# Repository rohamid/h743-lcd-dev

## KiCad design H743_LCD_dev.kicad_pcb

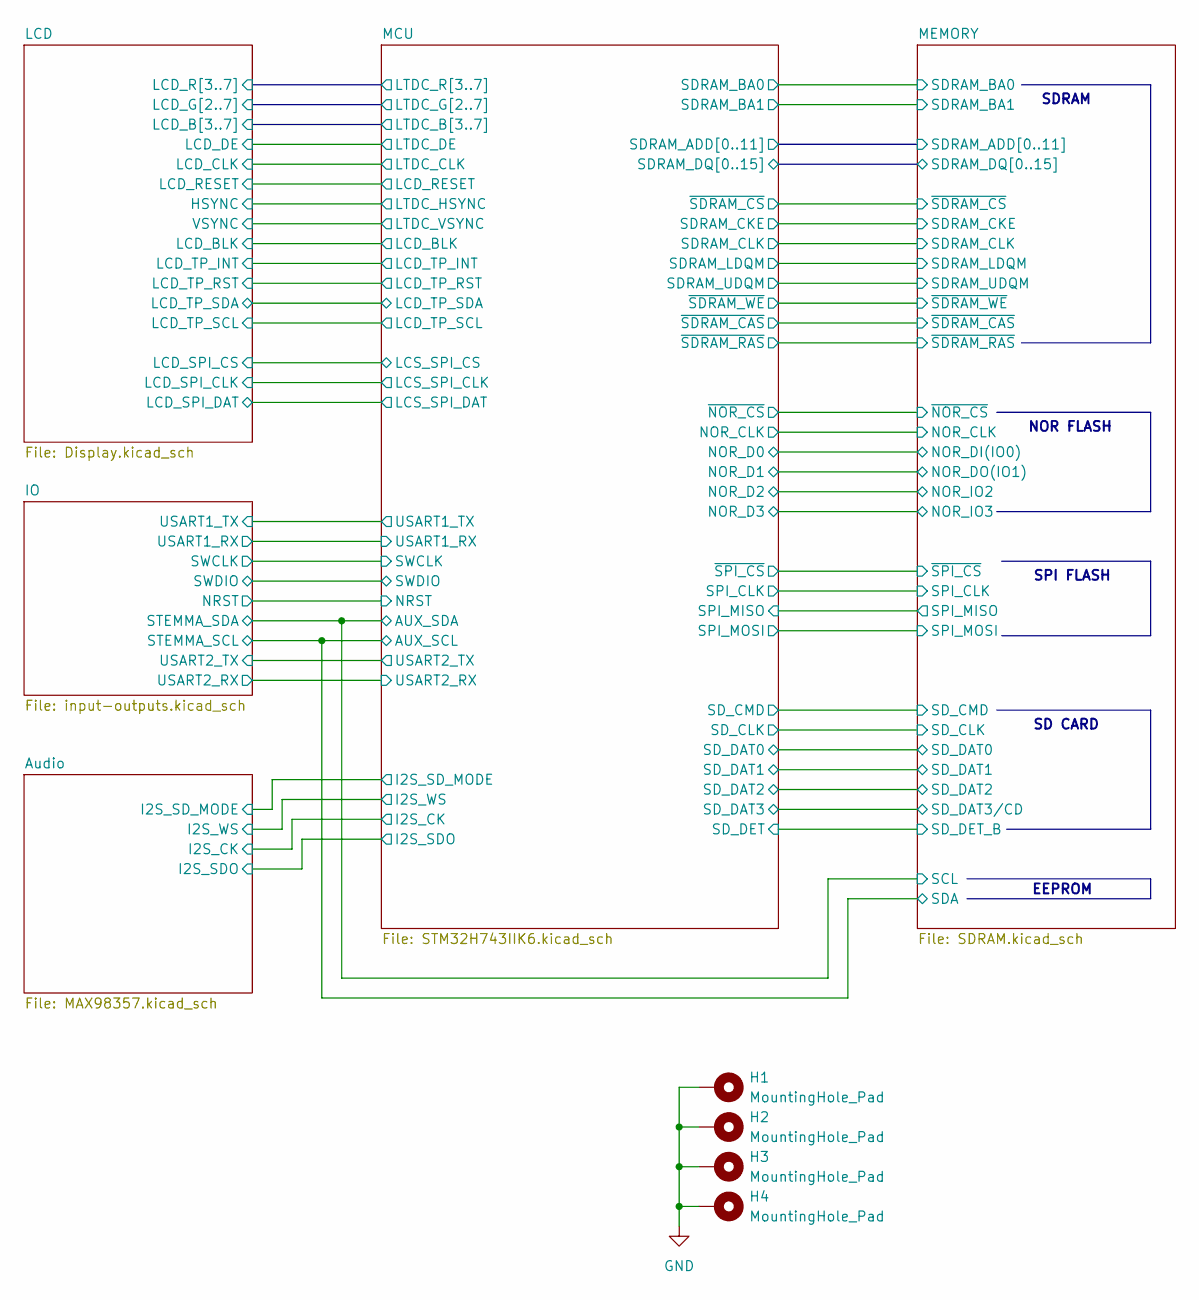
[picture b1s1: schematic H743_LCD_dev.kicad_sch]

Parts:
H1, H2, H3, H4: MountingHole_Pad; MountingHole_3.2mm_M3_Pad_Via

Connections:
GND: H1.1, H2.1, H3.1, H4.1; also elsewhere on the board

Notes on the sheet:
SD CARD
NOR FLASH
SPI FLASH
SDRAM
EEPROM

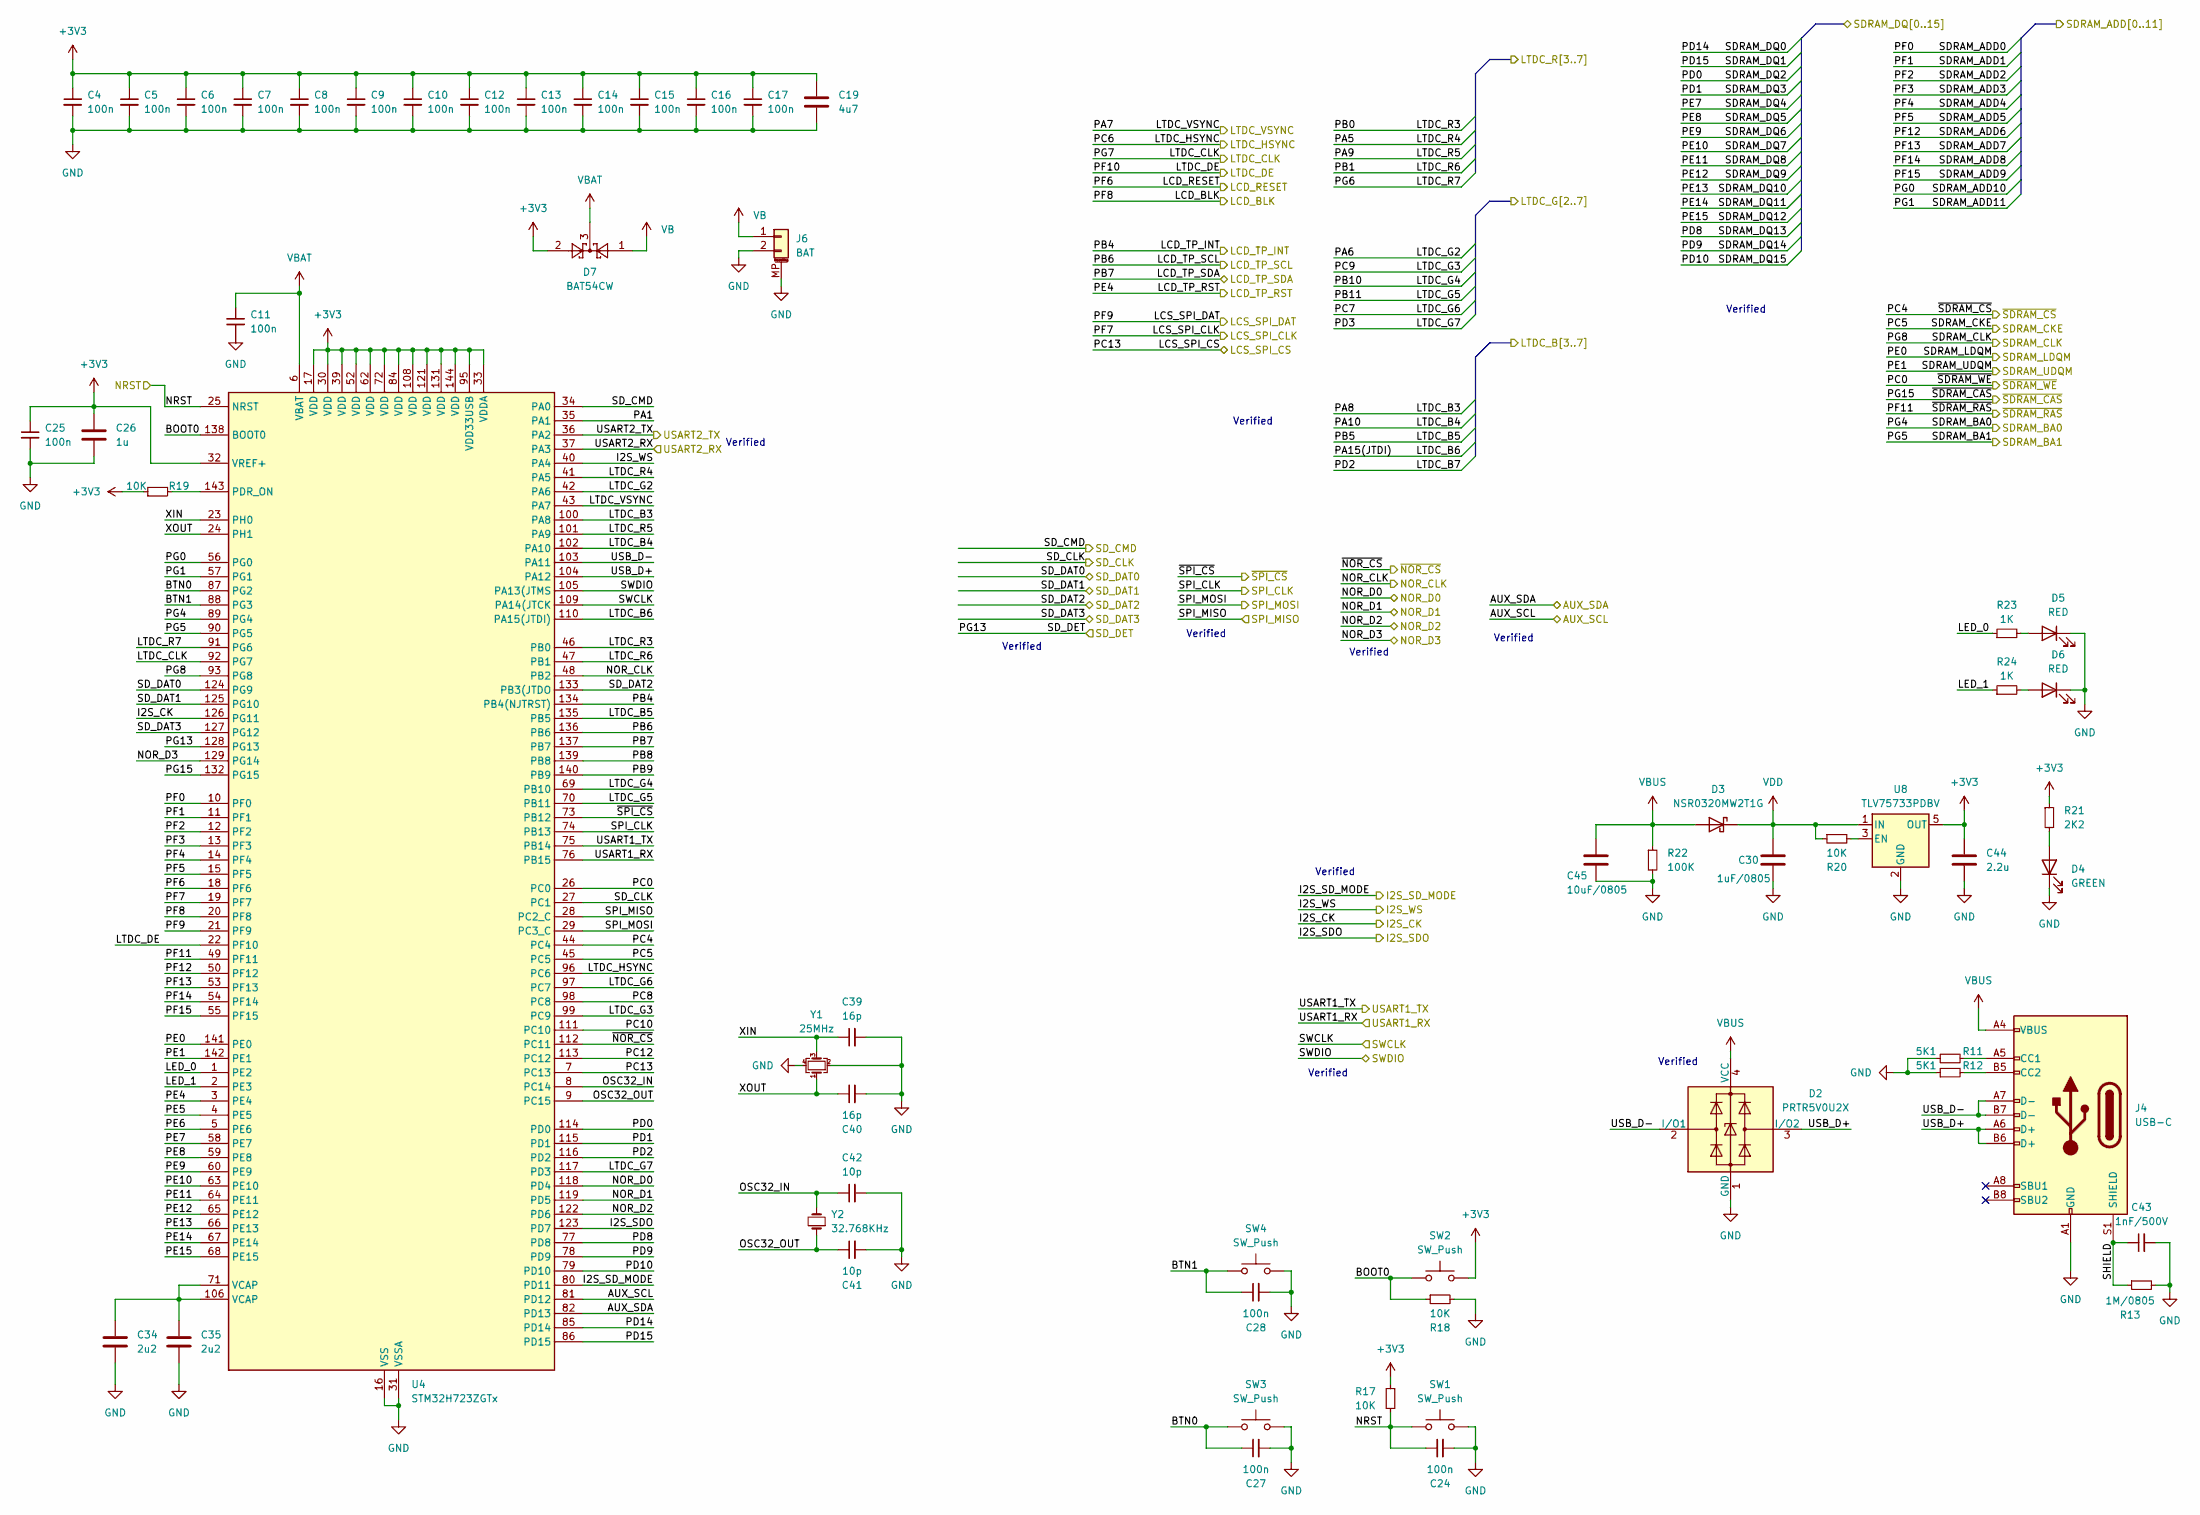
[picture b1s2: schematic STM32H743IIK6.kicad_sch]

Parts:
C4, C5, C6, C7, C8, C9, C10, C11, C12, C13, C14, C15, C16, C17, C24, C25, C27, C28: 100n; C_0402_1005Metric; JLCPCB Part # C307331
C19: 4u7; C_0603_1608Metric; JLCPCB Part # C19666
C26: 1u; C_0603_1608Metric; JLCPCB Part # C15849
C30: 1uF/0805; C_0805_2012Metric; JLCPCB Part # C28323
C34, C35: 2u2; C_0603_1608Metric; JLCPCB Part # C23630
C39, C40: 16p; C_0402_1005Metric; JLCPCB Part # C77590
C41, C42: 10p; C_0402_1005Metric; JLCPCB Part # C32949
C43: 1nF/500V; C_1206_3216Metric; JLCPCB Part # C35216
C44: 2.2u; C_0805_2012Metric; JLCPCB Part # C377773
C45: 10uF/0805; C_0805_2012Metric; JLCPCB Part # C440198
D2: PRTR5V0U2X; SOT-143; JLCPCB Part # C12333
D3: NSR0320MW2T1G; D_SOD-323; JLCPCB Part # C48192
D4: GREEN; LED_0805_2012Metric; JLCPCB Part # C2297
D5, D6: RED; LED_0805_2012Metric; JLCPCB Part # C84256
D7: BAT54CW; SOT-23; JLCPCB Part # C37704
J4: USB-C; USB_C_Receptacle_G-Switch_GT-USB-7010ASV; JLCPCB Part # C963412
J6: BAT; Hirose_DF13C_CL535-0402-2-51_1x02-1MP_P1.25mm_Vertical; JLCPCB Part # C7419891
R11, R12: 5K1; R_0402_1005Metric; JLCPCB Part # C25905
R13: 1M/0805; R_0805_2012Metric; JLCPCB Part # C17514
R17, R18, R19, R20: 10K; R_0402_1005Metric; JLCPCB Part # C25744
R21: 2K2; R_0402_1005Metric; JLCPCB Part # C25879
R22: 100K; R_0402_1005Metric; JLCPCB Part # C25741
R23, R24: 1K; R_0402_1005Metric; JLCPCB Part # C11702
SW1, SW2, SW3, SW4: SW_Push; SW_SPST_PTS810; JLCPCB Part # C127488
U4: STM32H723ZGTx; LQFP-144_20x20mm_P0.5mm; JLCPCB Part # C730146
U8: TLV75733PDBV; SOT-23-5; JLCPCB Part # C485517
Y1: 25MHz; Crystal_SMD_2520-4Pin_2.5x2.0mm; JLCPCB Part # C255954
Y2: 32.768KHz; Crystal_SMD_2012-2Pin_2.0x1.2mm; JLCPCB Part # C99009

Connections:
+3V3: C4.1, C5.1, C6.1, C7.1, C8.1, C9.1, C10.1, C12.1, C13.1, C14.1, C15.1, C16.1, C17.1, C19.1, C25.1, C26.1, C44.1, D7.2, R17.1, R19.1, R21.1, SW2.2, U4.17 (VDD), U4.30 (VDD), U4.32 (VREF+), U4.33 (VDDA), U4.39 (VDD), U4.52 (VDD), U4.62 (VDD), U4.72 (VDD), U4.84 (VDD), U4.95 (VDD33USB), U4.108 (VDD), U4.121 (VDD), U4.131 (VDD), U4.144 (VDD), U8.5 (OUT); also elsewhere on the board
/IO/NRST: C24.1, R17.2, SW1.1, U4.25 (NRST); also elsewhere on the board
/IO/STEMMA_SCL: U4.81 (PD12); also elsewhere on the board
/IO/STEMMA_SDA: U4.82 (PD13); also elsewhere on the board
/IO/SWCLK: U4.109 (PA14(JTCK); also elsewhere on the board
/IO/SWDIO: U4.105 (PA13(JTMS); also elsewhere on the board
/IO/USART1_RX: U4.76 (PB15); also elsewhere on the board
/IO/USART1_TX: U4.75 (PB14); also elsewhere on the board
/IO/USART2_RX: U4.37 (PA3); also elsewhere on the board
/IO/USART2_TX: U4.36 (PA2); also elsewhere on the board
/LCD/HSYNC: U4.96 (PC6); also elsewhere on the board
/LCD/LCD_B3: U4.100 (PA8); also elsewhere on the board
/LCD/LCD_B4: U4.102 (PA10); also elsewhere on the board
/LCD/LCD_B5: U4.135 (PB5); also elsewhere on the board
/LCD/LCD_B6: U4.110 (PA15(JTDI)); also elsewhere on the board
/LCD/LCD_B7: U4.116 (PD2); also elsewhere on the board
/LCD/LCD_BLK: U4.20 (PF8); also elsewhere on the board
/LCD/LCD_CLK: U4.92 (PG7); also elsewhere on the board
/LCD/LCD_DE: U4.22 (PF10); also elsewhere on the board
/LCD/LCD_G2: U4.42 (PA6); also elsewhere on the board
/LCD/LCD_G3: U4.99 (PC9); also elsewhere on the board
/LCD/LCD_G4: U4.69 (PB10); also elsewhere on the board
/LCD/LCD_G5: U4.70 (PB11); also elsewhere on the board
/LCD/LCD_G6: U4.97 (PC7); also elsewhere on the board
/LCD/LCD_G7: U4.117 (PD3); also elsewhere on the board
/LCD/LCD_R3: U4.46 (PB0); also elsewhere on the board
/LCD/LCD_R4: U4.41 (PA5); also elsewhere on the board
/LCD/LCD_R5: U4.101 (PA9); also elsewhere on the board
/LCD/LCD_R6: U4.47 (PB1); also elsewhere on the board
/LCD/LCD_R7: U4.91 (PG6); also elsewhere on the board
/LCD/LCD_RESET: U4.18 (PF6); also elsewhere on the board
/LCD/LCD_SPI_CLK: U4.19 (PF7); also elsewhere on the board
/LCD/LCD_SPI_CS: U4.7 (PC13); also elsewhere on the board
/LCD/LCD_SPI_DAT: U4.21 (PF9); also elsewhere on the board
/LCD/LCD_TP_INT: U4.134 (PB4(NJTRST)); also elsewhere on the board
/LCD/LCD_TP_RST: U4.3 (PE4); also elsewhere on the board
/LCD/LCD_TP_SCL: U4.136 (PB6); also elsewhere on the board
/LCD/LCD_TP_SDA: U4.137 (PB7); also elsewhere on the board
/LCD/VSYNC: U4.43 (PA7); also elsewhere on the board
/MCU/BOOT0: R18.1, SW2.1, U4.138 (BOOT0)
/MCU/BTN0: C27.1, SW3.1, U4.87 (PG2)
/MCU/BTN1: C28.1, SW4.1, U4.88 (PG3)
/MCU/I2S_CK: U4.126 (PG11); also elsewhere on the board
/MCU/I2S_SDO: U4.123 (PD7); also elsewhere on the board
/MCU/I2S_SD_MODE: U4.80 (PD11); also elsewhere on the board
/MCU/I2S_WS: U4.40 (PA4); also elsewhere on the board
/MCU/LED_0: R23.1, U4.1 (PE2)
/MCU/LED_1: R24.1, U4.2 (PE3)
/MCU/NOR_CLK: U4.48 (PB2); also elsewhere on the board
/MCU/NOR_D0: U4.118 (PD4); also elsewhere on the board
/MCU/NOR_D1: U4.119 (PD5); also elsewhere on the board
/MCU/NOR_D2: U4.122 (PD6); also elsewhere on the board
/MCU/NOR_D3: U4.129 (PG14); also elsewhere on the board
/MCU/OSC32_IN: C42.1, U4.8 (PC14), Y2.2
/MCU/OSC32_OUT: C41.1, U4.9 (PC15), Y2.1
/MCU/PA1: U4.35 (PA1)
/MCU/PB8: U4.139 (PB8)
/MCU/PB9: U4.140 (PB9)
/MCU/PC0: U4.26 (PC0); also elsewhere on the board
/MCU/PC4: U4.44 (PC4); also elsewhere on the board
/MCU/PC5: U4.45 (PC5); also elsewhere on the board
/MCU/PC8: U4.98 (PC8)
/MCU/PC10: U4.111 (PC10)
/MCU/PC12: U4.113 (PC12)
/MCU/PE0: U4.141 (PE0); also elsewhere on the board
/MCU/PE1: U4.142 (PE1); also elsewhere on the board
/MCU/PE5: U4.4 (PE5)
/MCU/PE6: U4.5 (PE6)
/MCU/PF11: U4.49 (PF11); also elsewhere on the board
/MCU/PG4: U4.89 (PG4); also elsewhere on the board
/MCU/PG5: U4.90 (PG5); also elsewhere on the board
/MCU/PG8: U4.93 (PG8); also elsewhere on the board
/MCU/PG13: U4.128 (PG13); also elsewhere on the board
/MCU/PG15: U4.132 (PG15); also elsewhere on the board
/MCU/SDRAM_ADD0: U4.10 (PF0); also elsewhere on the board
/MCU/SDRAM_ADD1: U4.11 (PF1); also elsewhere on the board
/MCU/SDRAM_ADD2: U4.12 (PF2); also elsewhere on the board
/MCU/SDRAM_ADD3: U4.13 (PF3); also elsewhere on the board
/MCU/SDRAM_ADD4: U4.14 (PF4); also elsewhere on the board
/MCU/SDRAM_ADD5: U4.15 (PF5); also elsewhere on the board
/MCU/SDRAM_ADD6: U4.50 (PF12); also elsewhere on the board
/MCU/SDRAM_ADD7: U4.53 (PF13); also elsewhere on the board
/MCU/SDRAM_ADD8: U4.54 (PF14); also elsewhere on the board
/MCU/SDRAM_ADD9: U4.55 (PF15); also elsewhere on the board
/MCU/SDRAM_ADD10: U4.56 (PG0); also elsewhere on the board
/MCU/SDRAM_ADD11: U4.57 (PG1); also elsewhere on the board
/MCU/SDRAM_DQ0: U4.85 (PD14); also elsewhere on the board
/MCU/SDRAM_DQ1: U4.86 (PD15); also elsewhere on the board
/MCU/SDRAM_DQ2: U4.114 (PD0); also elsewhere on the board
/MCU/SDRAM_DQ3: U4.115 (PD1); also elsewhere on the board
/MCU/SDRAM_DQ4: U4.58 (PE7); also elsewhere on the board
/MCU/SDRAM_DQ5: U4.59 (PE8); also elsewhere on the board
/MCU/SDRAM_DQ6: U4.60 (PE9); also elsewhere on the board
/MCU/SDRAM_DQ7: U4.63 (PE10); also elsewhere on the board
/MCU/SDRAM_DQ8: U4.64 (PE11); also elsewhere on the board
/MCU/SDRAM_DQ9: U4.65 (PE12); also elsewhere on the board
/MCU/SDRAM_DQ10: U4.66 (PE13); also elsewhere on the board
/MCU/SDRAM_DQ11: U4.67 (PE14); also elsewhere on the board
/MCU/SDRAM_DQ12: U4.68 (PE15); also elsewhere on the board
/MCU/SDRAM_DQ13: U4.77 (PD8); also elsewhere on the board
/MCU/SDRAM_DQ14: U4.78 (PD9); also elsewhere on the board
/MCU/SDRAM_DQ15: U4.79 (PD10); also elsewhere on the board
/MCU/SD_CLK: U4.27 (PC1); also elsewhere on the board
/MCU/SD_CMD: U4.34 (PA0); also elsewhere on the board
/MCU/SD_DAT0: U4.124 (PG9); also elsewhere on the board
/MCU/SD_DAT1: U4.125 (PG10); also elsewhere on the board
/MCU/SD_DAT2: U4.133 (PB3(JTDO); also elsewhere on the board
/MCU/SD_DAT3: U4.127 (PG12); also elsewhere on the board
/MCU/SHIELD: C43.1, J4.S1 (SHIELD), R13.1
/MCU/SPI_CLK: U4.74 (PB13); also elsewhere on the board
/MCU/SPI_MISO: U4.28 (PC2_C); also elsewhere on the board
/MCU/SPI_MOSI: U4.29 (PC3_C); also elsewhere on the board
/MCU/USB_D+: D2.3 (I/O2), J4.A6 (D+), J4.B6 (D+), U4.104 (PA12)
/MCU/USB_D-: D2.2 (I/O1), J4.A7 (D-), J4.B7 (D-), U4.103 (PA11)
/MCU/XIN: C39.1, U4.23 (PH0), Y1.3
/MCU/XOUT: C40.1, U4.24 (PH1), Y1.1
/MCU/~NOR_CS: U4.112 (PC11); also elsewhere on the board
/MCU/~SPI_CS: U4.73 (PB12); also elsewhere on the board
GND: C4.2, C5.2, C6.2, C7.2, C8.2, C9.2, C10.2, C11.2, C12.2, C13.2, C14.2, C15.2, C16.2, C17.2, C19.2, C24.2, C25.2, C26.2, C27.2, C28.2, C30.2, C34.2, C35.2, C39.2, C40.2, C41.2, C42.2, C43.2, C44.2, C45.2, D2.1 (GND), D4.1 (K), D5.1 (K), D6.1 (K), J4.A1 (GND), J4.A12 (GND), J4.B1 (GND), J4.B12 (GND), J6.2, J6.MP (MountPin), R11.1, R12.1, R13.2, R18.2, R22.2, SW1.2, SW3.2, SW4.2, U4.16 (VSS), U4.31 (VSSA), U4.38 (VSS), U4.51 (VSS), U4.61 (VSS), U4.83 (VSS), U4.94 (VSS), U4.107 (VSS), U4.120 (VSS), U4.130 (VSS), U8.2 (GND), Y1.2, Y1.4; also elsewhere on the board
unnamed: C34.1, C35.1, U4.71 (VCAP), U4.106 (VCAP)
unnamed: D4.2 (A), R21.2
unnamed: D5.2 (A), R23.2
unnamed: D6.2 (A), R24.2
unnamed: J4.A5 (CC1), R11.2
unnamed: J4.B5 (CC2), R12.2
unnamed: R19.2, U4.143 (PDR_ON)
unnamed: R20.2, U8.3 (EN)
VB: D7.1, J6.1
VBAT: C11.1, D7.3, U4.6 (VBAT)
VBUS: C45.1, D2.4 (VCC), D3.2 (A), J4.A4 (VBUS), J4.A9 (VBUS), J4.B4 (VBUS), J4.B9 (VBUS), R22.1
VDD: C30.1, D3.1 (K), R20.1, U8.1 (IN); also elsewhere on the board

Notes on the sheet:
Verified

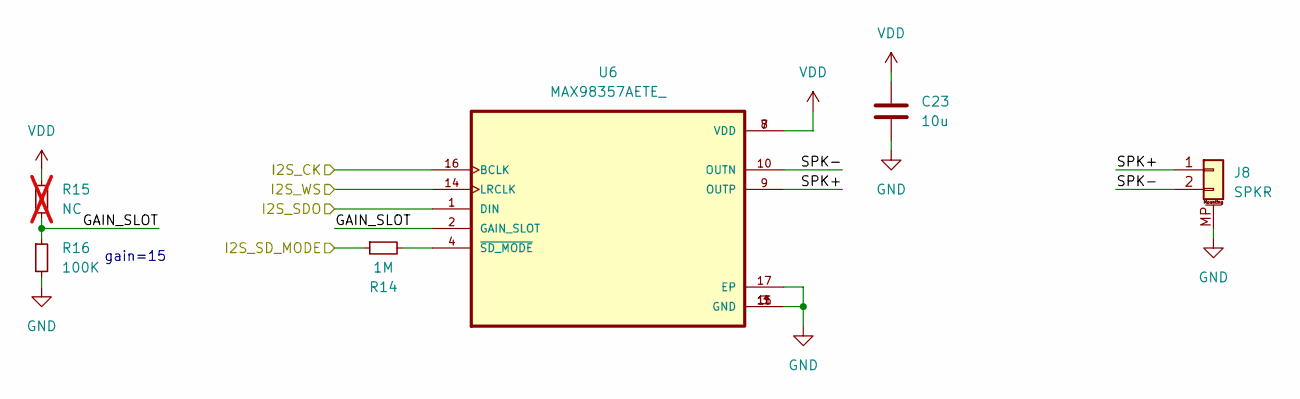
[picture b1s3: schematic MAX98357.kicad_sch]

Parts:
C23: 10u; C_0603_1608Metric; JLCPCB Part # C96446
J8: SPKR; Hirose_DF13C_CL535-0402-2-51_1x02-1MP_P1.25mm_Vertical; JLCPCB Part # C7419891
R14: 1M; R_0402_1005Metric; JLCPCB Part # C26083
R15: NC; R_0402_1005Metric; not fitted
R16: 100K; R_0402_1005Metric; JLCPCB Part # C25741
U6: MAX98357AETE_; QFN50P300X300X80-17N; JLCPCB Part # C910544

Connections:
/Audio/GAIN_SLOT: R15.2, R16.1, U6.2 (GAIN_SLOT)
/Audio/SPK+: J8.1, U6.9 (OUTP)
/Audio/SPK-: J8.2, U6.10 (OUTN)
/MCU/I2S_CK: U6.16 (BCLK); also elsewhere on the board
/MCU/I2S_SDO: U6.1 (DIN); also elsewhere on the board
/MCU/I2S_SD_MODE: R14.1; also elsewhere on the board
/MCU/I2S_WS: U6.14 (LRCLK); also elsewhere on the board
GND: C23.2, J8.MP (MountPin), R16.2, U6.3 (GND), U6.11 (GND), U6.15 (GND), U6.17 (EP); also elsewhere on the board
unnamed: R14.2, U6.4 (~SD_MODE)
VDD: C23.1, R15.1, U6.7 (VDD), U6.8 (VDD); also elsewhere on the board

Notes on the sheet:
gain=15

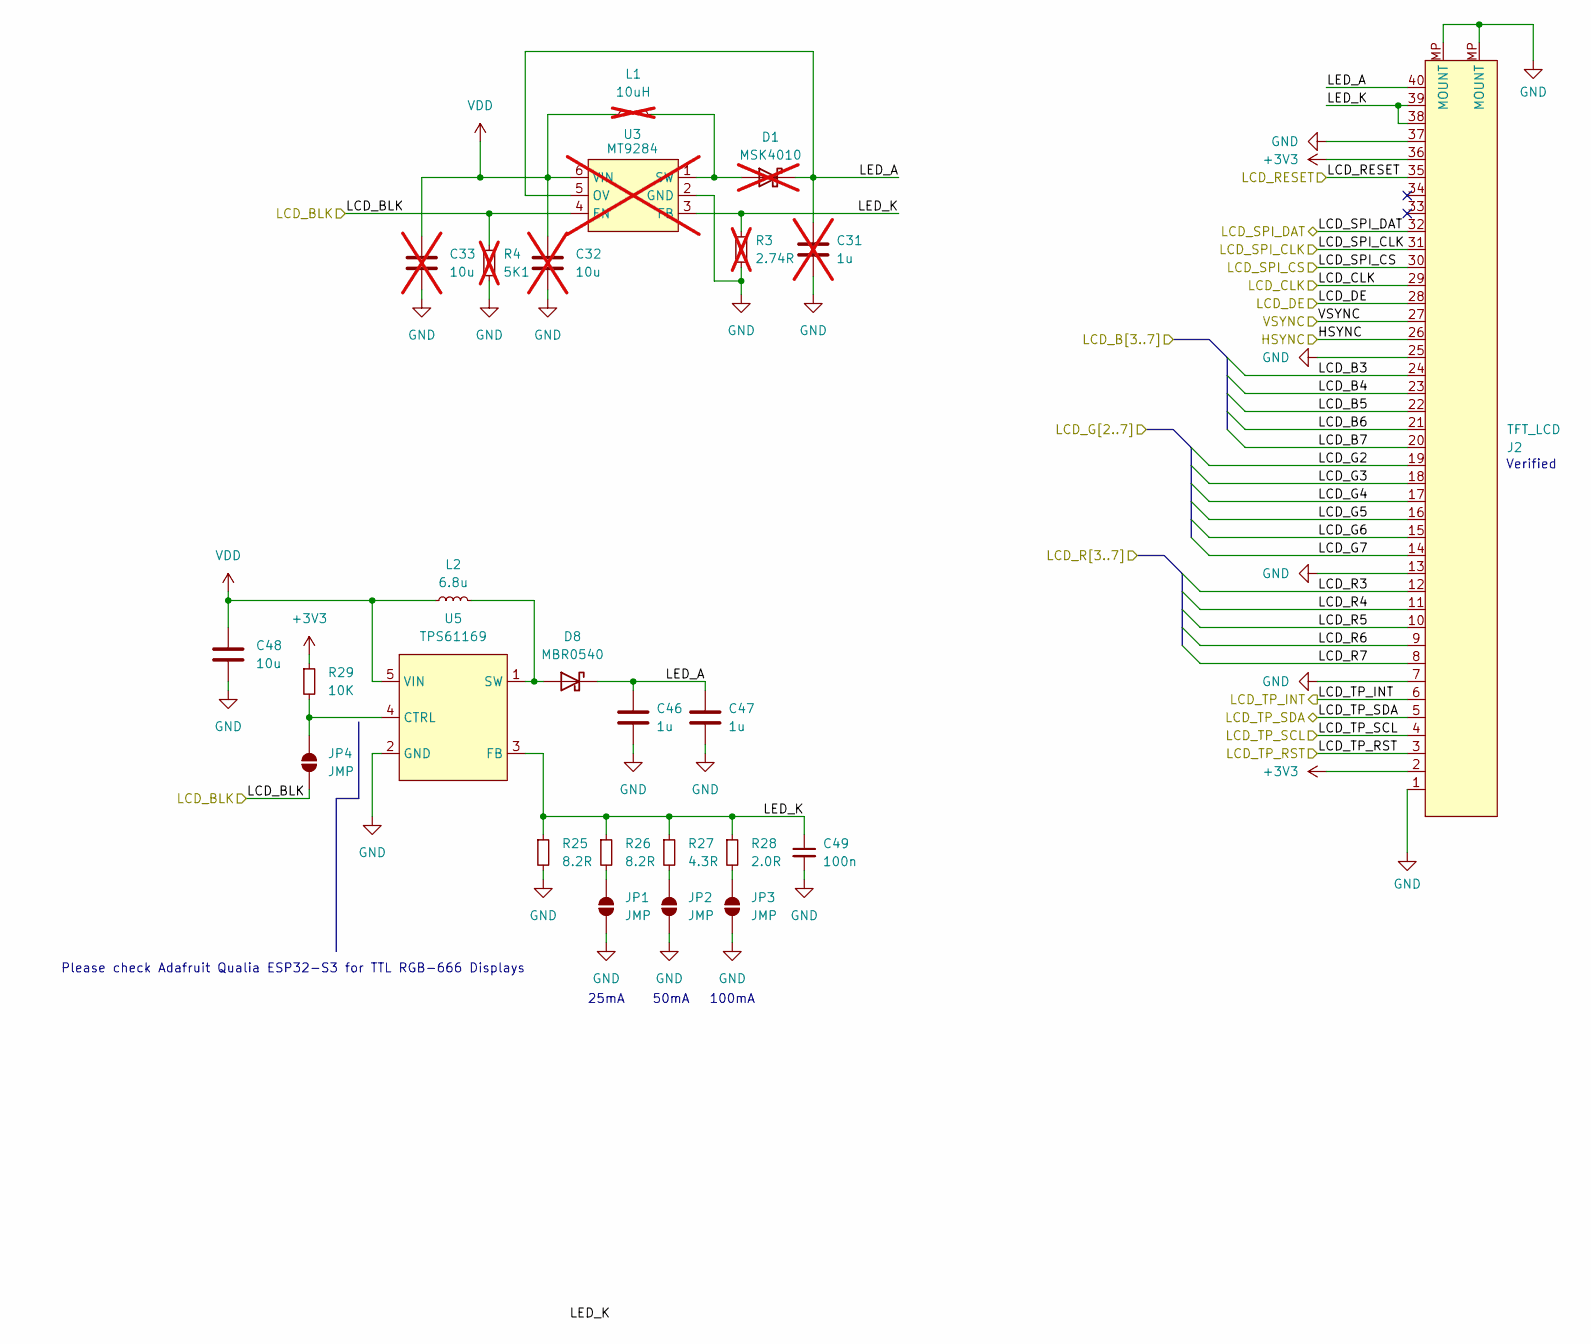
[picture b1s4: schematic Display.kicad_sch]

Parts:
C31: 1u; C_0603_1608Metric; JLCPCB Part # C15849; not fitted
C32, C33: 10u; C_0603_1608Metric; JLCPCB Part # C96446; not fitted
C46, C47: 1u; C_0603_1608Metric; JLCPCB Part # C15849
C48: 10u; C_0603_1608Metric; JLCPCB Part # C96446
C49: 100n; C_0402_1005Metric; JLCPCB Part # C307331
D1: MSK4010; D_SOD-523; JLCPCB Part # C345958; not fitted
D8: MBR0540; D_SOD-123; JLCPCB Part # C21353
J2: TFT_LCD; Omron-XF2M-4015-1A-R100-0-0-0; JLCPCB Part # C225713
JP1, JP2, JP3, JP4: JMP; SolderJumper-2_P1.3mm_Open_RoundedPad1.0x1.5mm
L1: 10uH; L_1210_3225Metric; JLCPCB Part # C189932; not fitted
L2: 6.8u; L_Changjiang_FNR5012S; JLCPCB Part # C2847472
R3: 2.74R; R_0402_1005Metric; JLCPCB Part # C166483; not fitted
R4: 5K1; R_0402_1005Metric; JLCPCB Part # C25905; not fitted
R25, R26: 8.2R; R_0402_1005Metric; JLCPCB Part # C514788
R27: 4.3R; R_0402_1005Metric; JLCPCB Part # C166641
R28: 2.0R; R_0402_1005Metric; JLCPCB Part # C203084
R29: 10K; R_0402_1005Metric; JLCPCB Part # C25744
U3: MT9284; SOT-23-6; JLCPCB Part # C181780; not fitted
U5: TPS61169; SOT-353_SC-70-5; JLCPCB Part # C71045

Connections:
+3V3: J2.2, J2.36, R29.1; also elsewhere on the board
/LCD/HSYNC: J2.26; also elsewhere on the board
/LCD/LCD_B3: J2.24; also elsewhere on the board
/LCD/LCD_B4: J2.23; also elsewhere on the board
/LCD/LCD_B5: J2.22; also elsewhere on the board
/LCD/LCD_B6: J2.21; also elsewhere on the board
/LCD/LCD_B7: J2.20; also elsewhere on the board
/LCD/LCD_BLK: JP4.1 (A), R4.1, U3.4 (EN); also elsewhere on the board
/LCD/LCD_CLK: J2.29; also elsewhere on the board
/LCD/LCD_DE: J2.28; also elsewhere on the board
/LCD/LCD_G2: J2.19; also elsewhere on the board
/LCD/LCD_G3: J2.18; also elsewhere on the board
/LCD/LCD_G4: J2.17; also elsewhere on the board
/LCD/LCD_G5: J2.16; also elsewhere on the board
/LCD/LCD_G6: J2.15; also elsewhere on the board
/LCD/LCD_G7: J2.14; also elsewhere on the board
/LCD/LCD_R3: J2.12; also elsewhere on the board
/LCD/LCD_R4: J2.11; also elsewhere on the board
/LCD/LCD_R5: J2.10; also elsewhere on the board
/LCD/LCD_R6: J2.9; also elsewhere on the board
/LCD/LCD_R7: J2.8; also elsewhere on the board
/LCD/LCD_RESET: J2.35; also elsewhere on the board
/LCD/LCD_SPI_CLK: J2.31; also elsewhere on the board
/LCD/LCD_SPI_CS: J2.30; also elsewhere on the board
/LCD/LCD_SPI_DAT: J2.32; also elsewhere on the board
/LCD/LCD_TP_INT: J2.6; also elsewhere on the board
/LCD/LCD_TP_RST: J2.3; also elsewhere on the board
/LCD/LCD_TP_SCL: J2.4; also elsewhere on the board
/LCD/LCD_TP_SDA: J2.5; also elsewhere on the board
/LCD/LED_A: C31.1, C46.1, C47.1, D1.1 (K), D8.1 (K), J2.40, U3.5 (OV)
/LCD/LED_K: C49.1, J2.38, J2.39, R3.1, R25.1, R26.1, R27.1, R28.1, U3.3 (FB), U5.3 (FB)
/LCD/VSYNC: J2.27; also elsewhere on the board
GND: C31.2, C32.2, C33.2, C46.2, C47.2, C48.2, C49.2, J2.1, J2.7, J2.13, J2.25, J2.37, J2.MP (MOUNT), JP1.1 (A), JP2.1 (A), JP3.1 (A), R3.2, R4.2, R25.2, U3.2 (GND), U5.2 (GND); also elsewhere on the board
unnamed: D1.2 (A), L1.2, U3.1 (SW)
unnamed: D8.2 (A), L2.2, U5.1 (SW)
unnamed: JP1.2 (B), R26.2
unnamed: JP2.2 (B), R27.2
unnamed: JP3.2 (B), R28.2
unnamed: JP4.2 (B), R29.2, U5.4 (CTRL)
VDD: C32.1, C33.1, C48.1, L1.1, L2.1, U3.6 (VIN), U5.5 (VIN); also elsewhere on the board

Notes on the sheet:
100mA
50mA
25mA
Verified
Please check Adafruit Qualia ESP32-S3 for TTL RGB-666 Displays

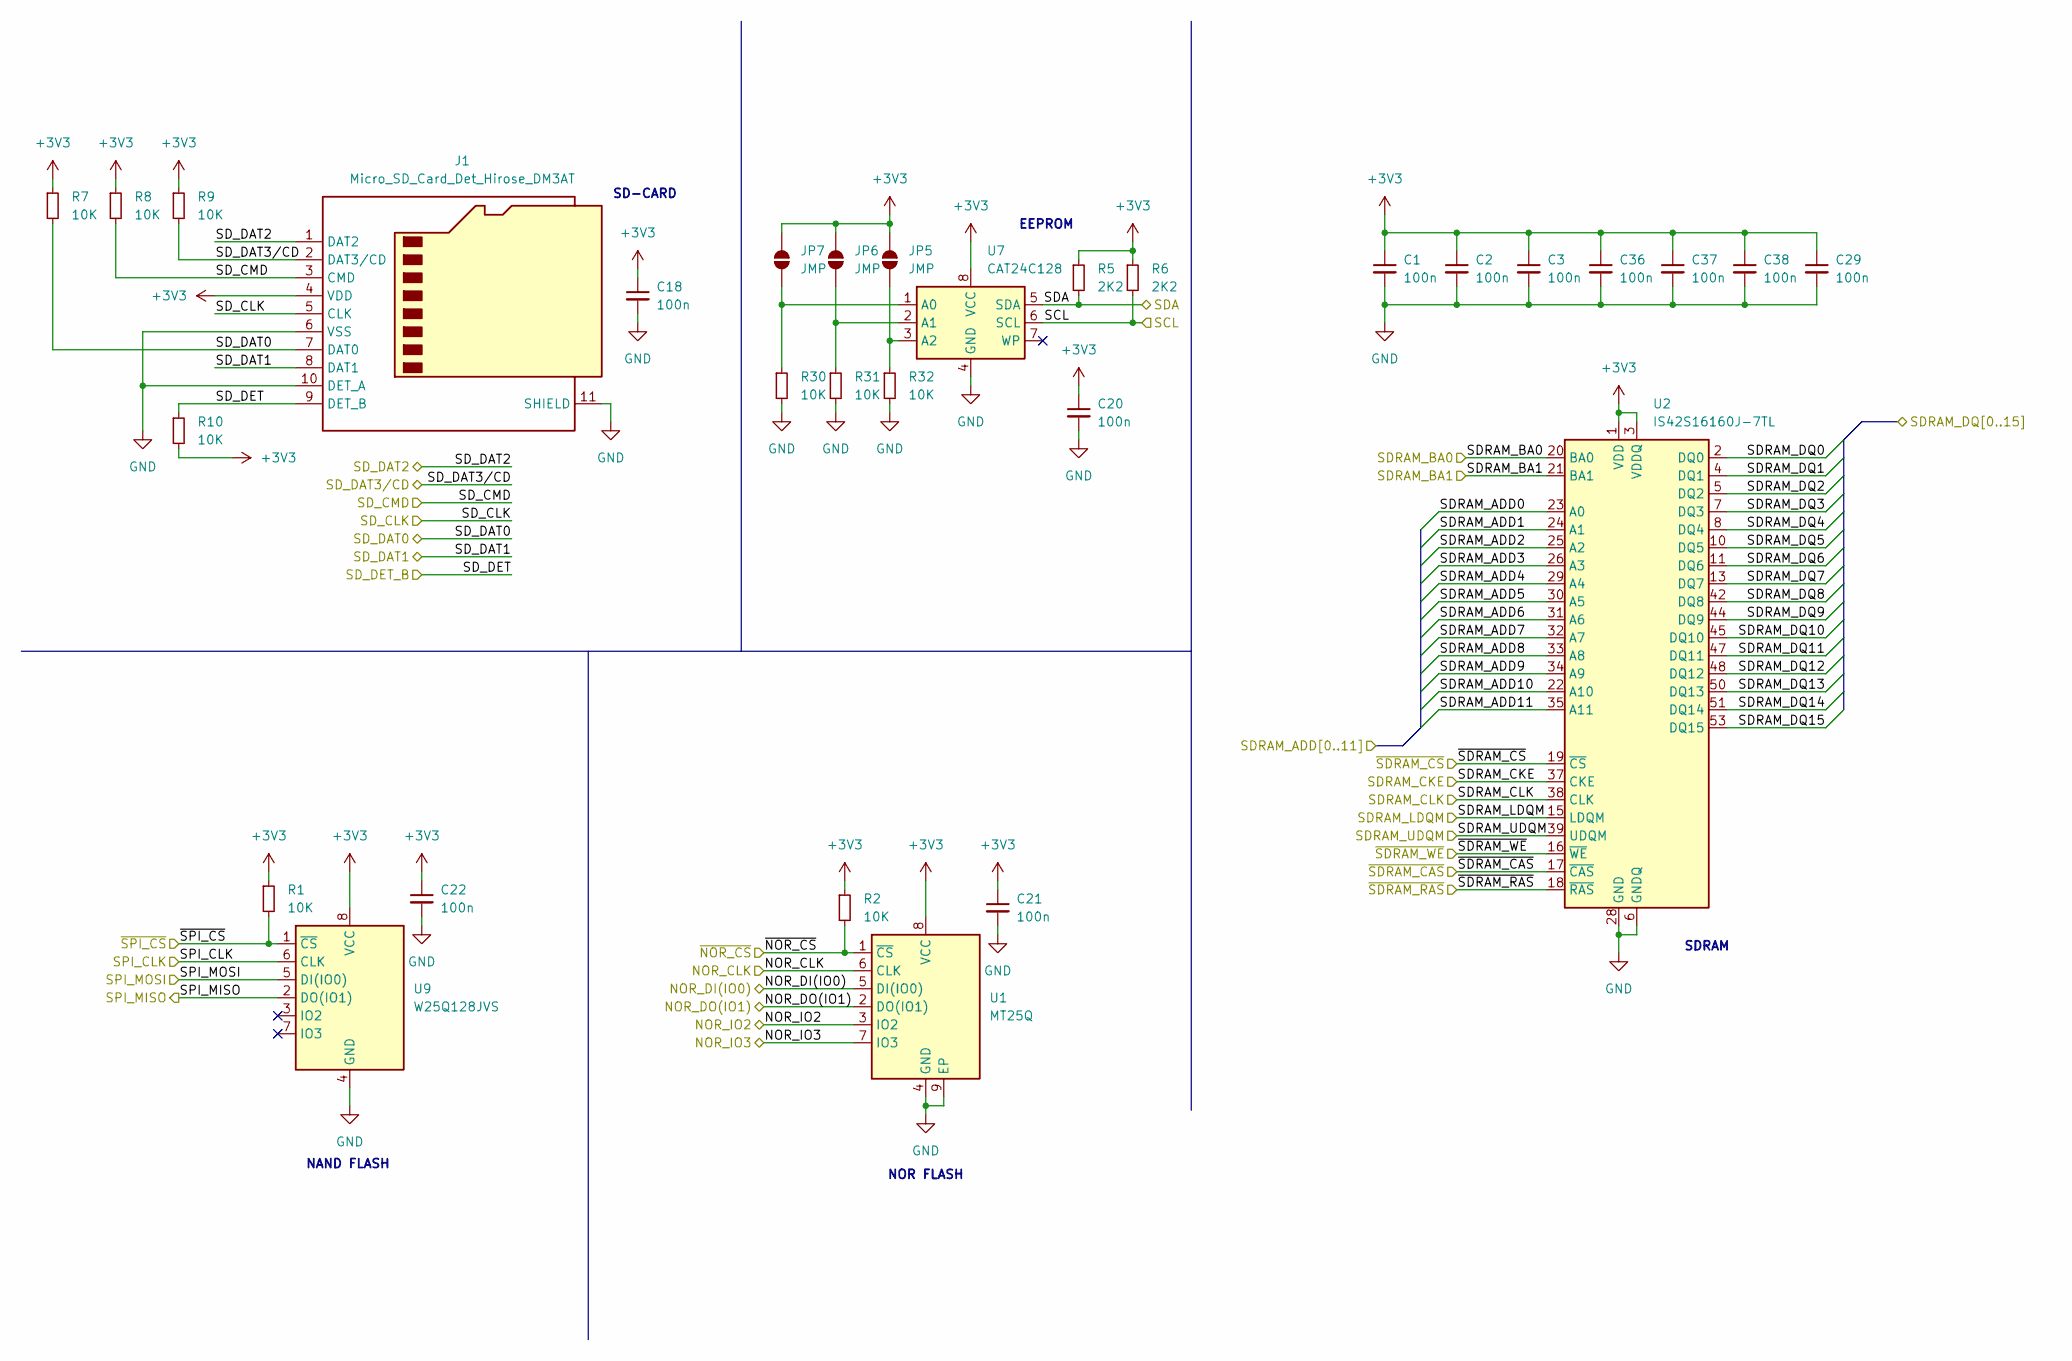
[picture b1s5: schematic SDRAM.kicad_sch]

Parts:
C1, C2, C3, C18, C20, C21, C22, C29, C36, C37, C38: 100n; C_0402_1005Metric; JLCPCB Part # C307331
J1: Micro_SD_Card_Det_Hirose_DM3AT; microSD_HC_Hirose_DM3AT-SF-PEJM5; JLCPCB Part # C114218
JP5, JP6, JP7: JMP; SolderJumper-2_P1.3mm_Open_RoundedPad1.0x1.5mm
R1, R2, R7, R8, R9, R10, R30, R31, R32: 10K; R_0402_1005Metric; JLCPCB Part # C25744
R5, R6: 2K2; R_0402_1005Metric; JLCPCB Part # C25879
U1: MT25Q; WSON-8-1EP_8x6mm_P1.27mm_EP3.4x4.3mm; JLCPCB Part # C2061007
U2: IS42S16160J-7TL; TSOP-II-54_22.2x10.16mm_P0.8mm; JLCPCB Part # C412833
U7: CAT24C128; SOIC-8_3.9x4.9mm_P1.27mm; JLCPCB Part # C6482
U9: W25Q128JVS; SOIC-8_5.23x5.23mm_P1.27mm; JLCPCB Part # C97521

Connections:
+3V3: C1.1, C2.1, C3.1, C18.1, C20.1, C21.1, C22.1, C29.1, C36.1, C37.1, C38.1, J1.4 (VDD), JP5.2 (B), JP6.2 (B), JP7.2 (B), R1.1, R2.1, R5.1, R6.1, R7.1, R8.1, R9.1, R10.2, U1.8 (VCC), U2.1 (VDD), U2.3 (VDDQ), U2.9 (VDDQ), U2.14 (VDD), U2.27 (VDD), U2.43 (VDDQ), U2.49 (VDDQ), U7.8 (VCC), U9.8 (VCC); also elsewhere on the board
/IO/STEMMA_SCL: R5.2, U7.5 (SDA); also elsewhere on the board
/IO/STEMMA_SDA: R6.2, U7.6 (SCL); also elsewhere on the board
/MCU/NOR_CLK: U1.6 (CLK); also elsewhere on the board
/MCU/NOR_D0: U1.5 (DI(IO0)); also elsewhere on the board
/MCU/NOR_D1: U1.2 (DO(IO1)); also elsewhere on the board
/MCU/NOR_D2: U1.3 (IO2); also elsewhere on the board
/MCU/NOR_D3: U1.7 (IO3); also elsewhere on the board
/MCU/PC0: U2.16 (~WE); also elsewhere on the board
/MCU/PC4: U2.19 (~CS); also elsewhere on the board
/MCU/PC5: U2.37 (CKE); also elsewhere on the board
/MCU/PE0: U2.15 (LDQM); also elsewhere on the board
/MCU/PE1: U2.39 (UDQM); also elsewhere on the board
/MCU/PF11: U2.18 (~RAS); also elsewhere on the board
/MCU/PG4: U2.20 (BA0); also elsewhere on the board
/MCU/PG5: U2.21 (BA1); also elsewhere on the board
/MCU/PG8: U2.38 (CLK); also elsewhere on the board
/MCU/PG13: J1.9 (DET_B), R10.1; also elsewhere on the board
/MCU/PG15: U2.17 (~CAS); also elsewhere on the board
/MCU/SDRAM_ADD0: U2.23 (A0); also elsewhere on the board
/MCU/SDRAM_ADD1: U2.24 (A1); also elsewhere on the board
/MCU/SDRAM_ADD2: U2.25 (A2); also elsewhere on the board
/MCU/SDRAM_ADD3: U2.26 (A3); also elsewhere on the board
/MCU/SDRAM_ADD4: U2.29 (A4); also elsewhere on the board
/MCU/SDRAM_ADD5: U2.30 (A5); also elsewhere on the board
/MCU/SDRAM_ADD6: U2.31 (A6); also elsewhere on the board
/MCU/SDRAM_ADD7: U2.32 (A7); also elsewhere on the board
/MCU/SDRAM_ADD8: U2.33 (A8); also elsewhere on the board
/MCU/SDRAM_ADD9: U2.34 (A9); also elsewhere on the board
/MCU/SDRAM_ADD10: U2.22 (A10); also elsewhere on the board
/MCU/SDRAM_ADD11: U2.35 (A11); also elsewhere on the board
/MCU/SDRAM_DQ0: U2.2 (DQ0); also elsewhere on the board
/MCU/SDRAM_DQ1: U2.4 (DQ1); also elsewhere on the board
/MCU/SDRAM_DQ2: U2.5 (DQ2); also elsewhere on the board
/MCU/SDRAM_DQ3: U2.7 (DQ3); also elsewhere on the board
/MCU/SDRAM_DQ4: U2.8 (DQ4); also elsewhere on the board
/MCU/SDRAM_DQ5: U2.10 (DQ5); also elsewhere on the board
/MCU/SDRAM_DQ6: U2.11 (DQ6); also elsewhere on the board
/MCU/SDRAM_DQ7: U2.13 (DQ7); also elsewhere on the board
/MCU/SDRAM_DQ8: U2.42 (DQ8); also elsewhere on the board
/MCU/SDRAM_DQ9: U2.44 (DQ9); also elsewhere on the board
/MCU/SDRAM_DQ10: U2.45 (DQ10); also elsewhere on the board
/MCU/SDRAM_DQ11: U2.47 (DQ11); also elsewhere on the board
/MCU/SDRAM_DQ12: U2.48 (DQ12); also elsewhere on the board
/MCU/SDRAM_DQ13: U2.50 (DQ13); also elsewhere on the board
/MCU/SDRAM_DQ14: U2.51 (DQ14); also elsewhere on the board
/MCU/SDRAM_DQ15: U2.53 (DQ15); also elsewhere on the board
/MCU/SD_CLK: J1.5 (CLK); also elsewhere on the board
/MCU/SD_CMD: J1.3 (CMD), R8.2; also elsewhere on the board
/MCU/SD_DAT0: J1.7 (DAT0), R7.2; also elsewhere on the board
/MCU/SD_DAT1: J1.8 (DAT1); also elsewhere on the board
/MCU/SD_DAT2: J1.1 (DAT2); also elsewhere on the board
/MCU/SD_DAT3: J1.2 (DAT3/CD), R9.2; also elsewhere on the board
/MCU/SPI_CLK: U9.6 (CLK); also elsewhere on the board
/MCU/SPI_MISO: U9.2 (DO(IO1)); also elsewhere on the board
/MCU/SPI_MOSI: U9.5 (DI(IO0)); also elsewhere on the board
/MCU/~NOR_CS: R2.2, U1.1 (~CS); also elsewhere on the board
/MCU/~SPI_CS: R1.2, U9.1 (~CS); also elsewhere on the board
GND: C1.2, C2.2, C3.2, C18.2, C20.2, C21.2, C22.2, C29.2, C36.2, C37.2, C38.2, J1.6 (VSS), J1.10 (DET_A), J1.11 (SHIELD), R30.2, R31.2, R32.2, U1.4 (GND), U1.9 (EP), U2.6 (GNDQ), U2.12 (GNDQ), U2.28 (GND), U2.41 (GND), U2.46 (GNDQ), U2.52 (GNDQ), U2.54 (GND), U7.4 (GND), U9.4 (GND); also elsewhere on the board
unnamed: JP5.1 (A), R32.1, U7.3 (A2)
unnamed: JP6.1 (A), R31.1, U7.2 (A1)
unnamed: JP7.1 (A), R30.1, U7.1 (A0)

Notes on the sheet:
NOR FLASH
SD-CARD
SDRAM
EEPROM
NAND FLASH
